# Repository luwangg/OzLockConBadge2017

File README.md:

# OzLockConBadge2017
Hardware and Firmware for the OzLockCon2017 Badge

Derived from the uDuck:
https://github.com/insecurityofthings/uDuck - as you can probably tell from the source code.

The hardware *may* support the uDuck firmware as the circuit is based off it - but i screwed something up and it doesn't want to work.
Ran out of time to debug so focused on the flashy flashy.

# Warning!
don't solder the USB connector onto the badge until you check the pin out! 
i screwed up and reversed the pads on the footprint - again...

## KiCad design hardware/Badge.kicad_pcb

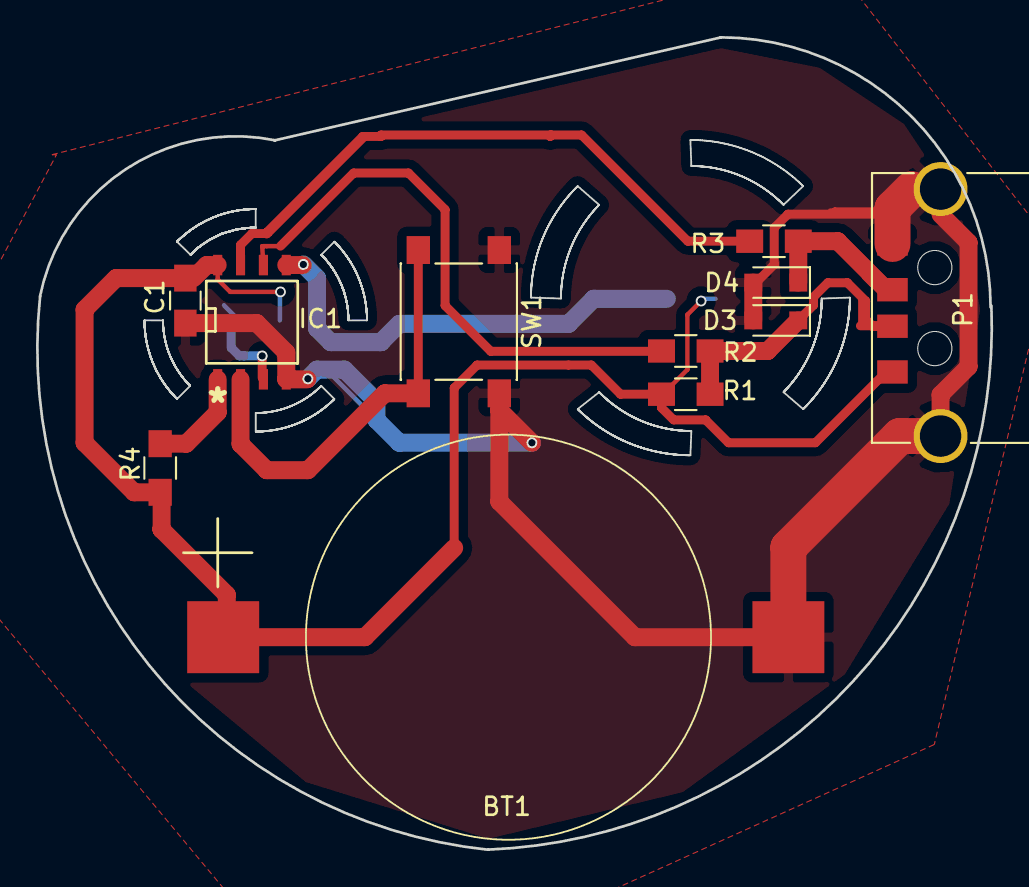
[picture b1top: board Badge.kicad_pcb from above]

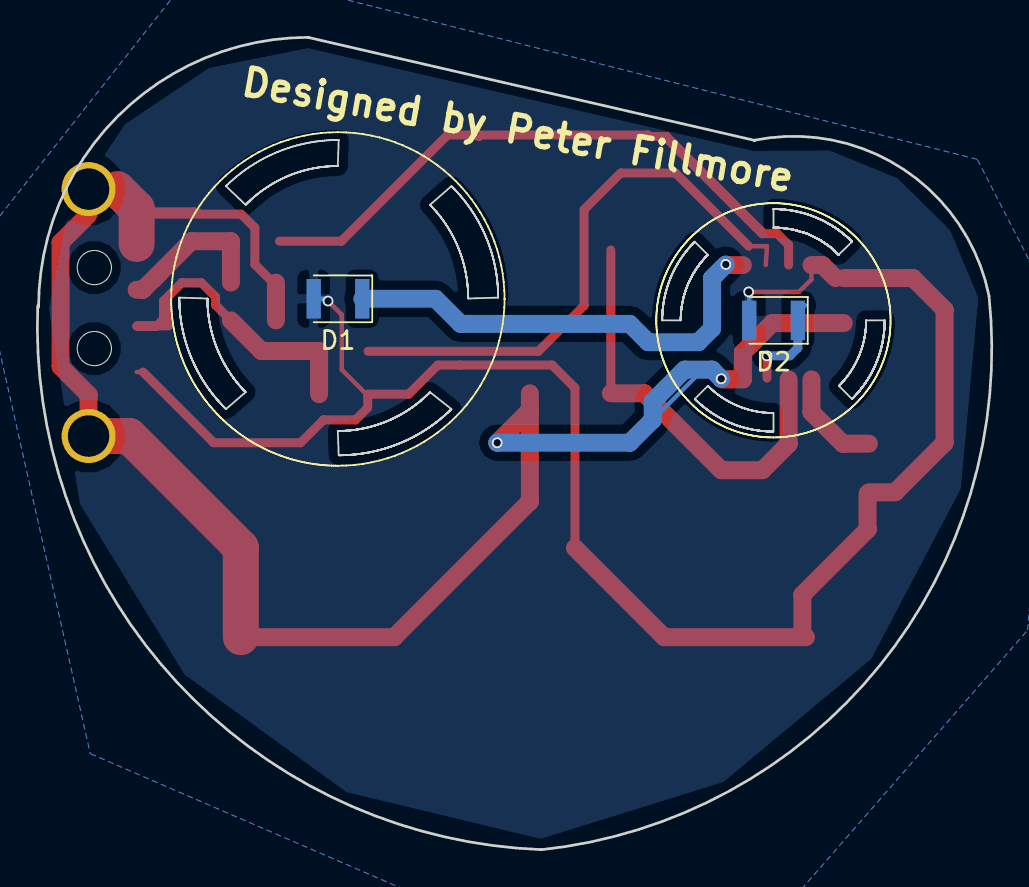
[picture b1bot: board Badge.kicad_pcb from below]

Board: 2 copper layers, 53.0 x 45.1 mm, 13 parts (2 on the bottom side), 10 nets.

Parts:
BT1: Battery; CR2032_SMD
C1: 0.1uF; C_0805_HandSoldering
D1, D2: LED; LED_3528
D3, D4: ZENER; D_SOD-323_HandSoldering
IC1: ATTINY85-S; SOIC-8-N
P1: USB_A; USB_A_SMD
R1: 1.5k; R_0805_HandSoldering
R2, R3: 68; R_0805_HandSoldering
R4: 10k; R_0805_HandSoldering
SW1: SW_PUSH; SW_SPST_PTS645

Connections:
D_MINUS: D3.1, P1.2, R1.2, R2.2
D_PLUS: D4.1, P1.3, R3.2
GND: BT1.2, C1.2, D3.2, D4.2, IC1.4, P1.4, P1.5, SW1.1
LED_LEFT: D1.1, IC1.5
LED_RIGHT: D2.1, IC1.3
unnamed: IC1.1, R4.1
SW1: IC1.2, SW1.2
UC_D_MINUS: IC1.6, R2.1
UC_D_PLUS: IC1.7, R3.1
VCC: BT1.1, C1.1, D1.2, D2.2, IC1.8, P1.1, R1.1, R4.2

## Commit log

2017-06-04 inital commit
2017-06-04 now with added schematic
